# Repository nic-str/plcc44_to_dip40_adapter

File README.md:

# PLC-44 to DIP-40 Adapter for EPROMs

e.g. 27CXX

Not suitable for MCUs.

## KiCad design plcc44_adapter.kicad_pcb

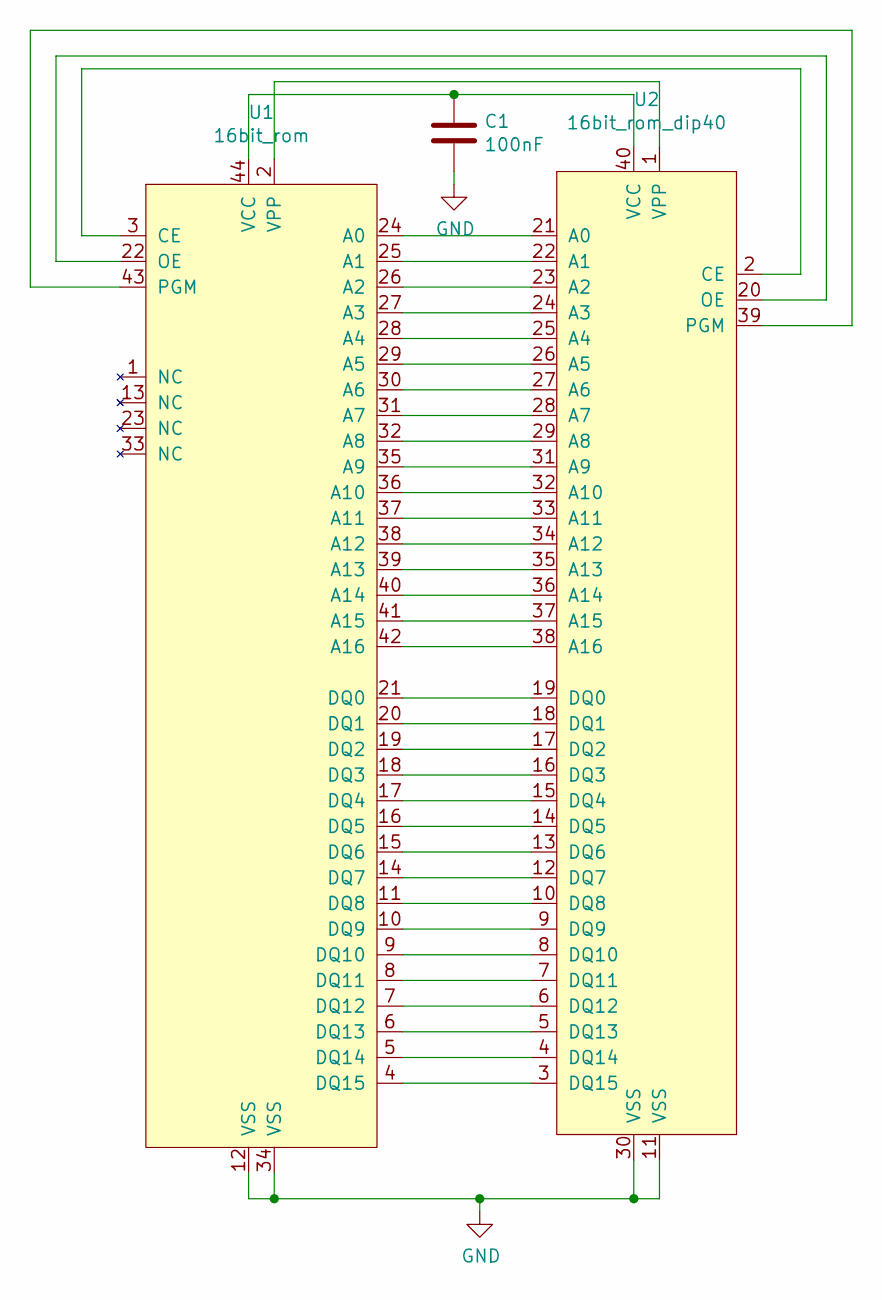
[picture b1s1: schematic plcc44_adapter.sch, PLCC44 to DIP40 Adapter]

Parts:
C1: 100nF; C_0603_1608Metric
U1: 16bit_rom; PLCC-44_THT-Socket_mod
U2: 16bit_rom_dip40; DIP-40_W15.24mm_mod

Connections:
GND: C1.2, U1.12 (VSS), U1.34 (VSS), U2.11 (VSS), U2.30 (VSS)
unnamed: C1.1, U1.44 (VCC), U2.40 (VCC)
unnamed: U1.2 (VPP), U2.1 (VPP)
unnamed: U1.3 (CE), U2.2 (CE)
unnamed: U1.4 (DQ15), U2.3 (DQ15)
unnamed: U1.5 (DQ14), U2.4 (DQ14)
unnamed: U1.6 (DQ13), U2.5 (DQ13)
unnamed: U1.7 (DQ12), U2.6 (DQ12)
unnamed: U1.8 (DQ11), U2.7 (DQ11)
unnamed: U1.9 (DQ10), U2.8 (DQ10)
unnamed: U1.10 (DQ9), U2.9 (DQ9)
unnamed: U1.11 (DQ8), U2.10 (DQ8)
unnamed: U1.14 (DQ7), U2.12 (DQ7)
unnamed: U1.15 (DQ6), U2.13 (DQ6)
unnamed: U1.16 (DQ5), U2.14 (DQ5)
unnamed: U1.17 (DQ4), U2.15 (DQ4)
unnamed: U1.18 (DQ3), U2.16 (DQ3)
unnamed: U1.19 (DQ2), U2.17 (DQ2)
unnamed: U1.20 (DQ1), U2.18 (DQ1)
unnamed: U1.21 (DQ0), U2.19 (DQ0)
unnamed: U1.22 (OE), U2.20 (OE)
unnamed: U1.24 (A0), U2.21 (A0)
unnamed: U1.25 (A1), U2.22 (A1)
unnamed: U1.26 (A2), U2.23 (A2)
unnamed: U1.27 (A3), U2.24 (A3)
unnamed: U1.28 (A4), U2.25 (A4)
unnamed: U1.29 (A5), U2.26 (A5)
unnamed: U1.30 (A6), U2.27 (A6)
unnamed: U1.31 (A7), U2.28 (A7)
unnamed: U1.32 (A8), U2.29 (A8)
unnamed: U1.35 (A9), U2.31 (A9)
unnamed: U1.36 (A10), U2.32 (A10)
unnamed: U1.37 (A11), U2.33 (A11)
unnamed: U1.38 (A12), U2.34 (A12)
unnamed: U1.39 (A13), U2.35 (A13)
unnamed: U1.40 (A14), U2.36 (A14)
unnamed: U1.41 (A15), U2.37 (A15)
unnamed: U1.42 (A16), U2.38 (A16)
unnamed: U1.43 (PGM), U2.39 (PGM)

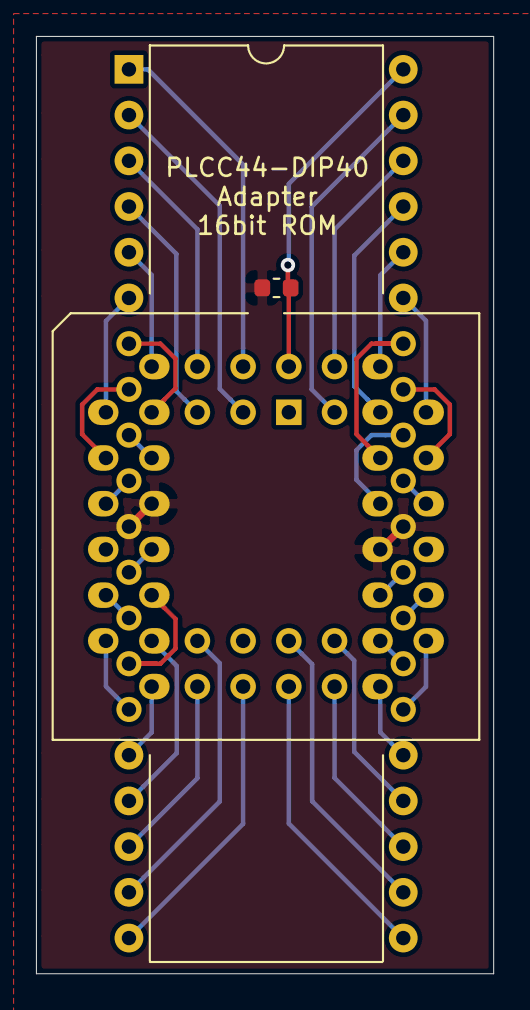
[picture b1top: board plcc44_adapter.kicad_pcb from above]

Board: 2 copper layers, 25.4 x 52.1 mm, 3 parts (0 on the bottom side), 39 nets.

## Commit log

2020-04-26 „README.md“ hinzufügen
2020-04-26 Added PLC44 Symbol
2020-04-26 Updated Symbols Updates Footprints for easier soldering
2020-04-26 Added Gerber Files Updated README Updated Layout
2020-05-06 .gitignore is now working
2020-05-06 Added Info to schematic and layout
2020-05-10 Create LICENSE
2020-05-16 Updated Footprint
2020-05-16 Updated 3D Render
2020-05-16 Updated Gerber Files
